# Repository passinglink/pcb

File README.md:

### Passing Link PCB designs
This is a dumping ground for PCB designs for [Passing Link](https://github.com/passinglink/passinglink).

Designs are implemented in [Horizon EDA](https://horizon-eda.org/). To load them, add `./pool` to
your pools in Horizon's settings.

Current designs:
- [microdash](microdash/) - a minimal hitbox
- [module](module/) - passinglink on an M.2 module, that can be assembled directly by JLCPCB
  - [panthera](panthera/) - an adapter board for `module`

Legacy KiCAD designs:
  - Razer Panthera
    - [STM32](panthera_stm32/)
    - [NRF52840](panthera_e73/)

### Copying
Unless otherwise specified, everything in this repository is licensed under the MIT license.

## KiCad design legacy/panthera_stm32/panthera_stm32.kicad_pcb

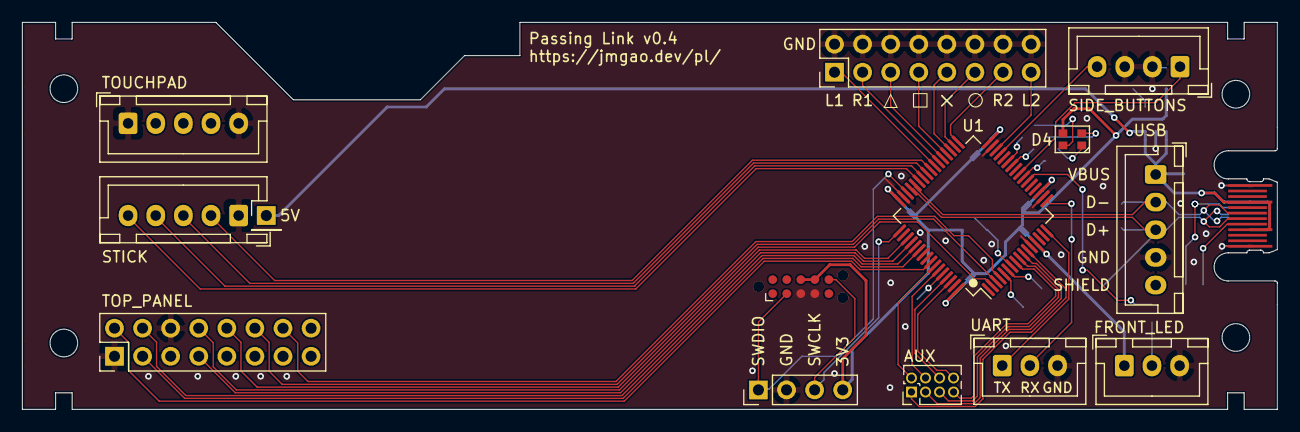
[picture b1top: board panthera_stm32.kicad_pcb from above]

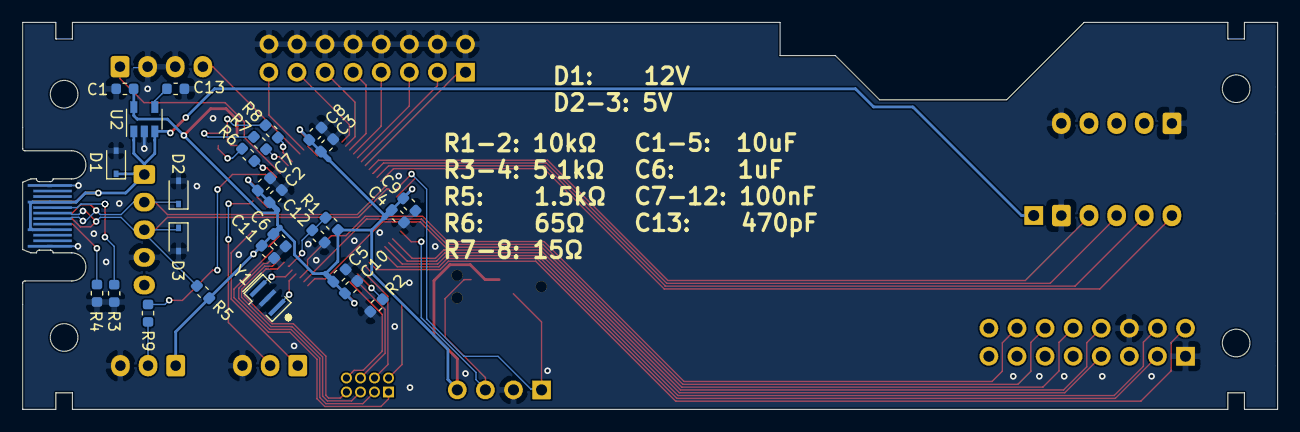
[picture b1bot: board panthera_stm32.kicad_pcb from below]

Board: 2 copper layers, 113.5 x 35.0 mm, 47 parts (32 on the bottom side), 59 nets.

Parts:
C1, C2, C3, C4, C5: 10uF; C_0603_1608Metric
C6: 1uF; C_0603_1608Metric
C7, C8, C9, C10, C11, C12: 100nF; C_0603_1608Metric
C13: 470pF; C_0603_1608Metric
D1: PESD12VL1BA,115; D_SOD-323
D2, D3: PESD5V0L1BA,115; D_SOD-323
D4: FM-B2020RGBA-HG
J1: Conn_01x05_Female; JST_XH_B5B-XH-A_1x05_P2.50mm_Vertical
J2: Conn_01x04; PinHeader_1x04_P2.54mm_Vertical
J3: Conn_02x05_Odd_Even; Tag-Connect_TC2050-IDC-NL_2x05_P1.27mm_Vertical
J4, J5: Conn_01x05; JST_XH_B5B-XH-A_1x05_P2.50mm_Vertical
J6, J7: Conn_02x08_Odd_Even; PinHeader_2x08_P2.54mm_Vertical
J8, J9: Conn_01x03; JST_XH_B3B-XH-A_1x03_P2.50mm_Vertical
J10: Conn_02x04_Odd_Even; PinHeader_2x04_P1.27mm_Vertical
J11: Conn_01x01; PinHeader_1x01_P2.54mm_Vertical
J12: Conn_01x04; JST_XH_B4B-XH-A_1x04_P2.50mm_Vertical
NT1, NT2, NT3, NT4, NT5: Net-Tie_2; NetTie-2_SMD_Pad0.5mm
R1, R2: 10K; R_0603_1608Metric
R3, R4: 5.1K; R_0603_1608Metric
R5: 1.5K; R_0603_1608Metric
R6: 65; R_0603_1608Metric
R7, R8: 15; R_0603_1608Metric
R9: 100; R_0603_1608Metric
U1: STM32F103RETx; LQFP-64_10x10mm_P0.5mm
U2: MIC5219-3.3YM5; SOT-23-5
X1: PCB-USB-C
Y1: Crystal_GND2_Small; Resonator_SMD_muRata_CSTxExxV-3Pin_3.0x1.1mm

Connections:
+3V3: C1.1, D4.3, J2.4, J3.7, J3.8, NT1.1, NT2.1, NT3.1, NT4.1, NT5.1, R1.2, U2.5
/BOOT0: R2.1, U1.60
/NRST: C12.1, R1.1, U1.7
/OSC_IN: U1.5, Y1.3
/OSC_OUT: U1.6, Y1.1
/PA2_UART_TX: J9.1, U1.16
/PA3_UART_RX: J9.2, U1.17
/PA6_FRONT_LED_K: R9.2, U1.22
/PA7_LED_R_K: R6.1, U1.23
/PA8_STICK_LEFT: J5.3, U1.41
/PA9_STICK_UP: J5.4, U1.42
/PA10_STICK_DOWN: J5.5, U1.43
/PB0_LED_G_K: R7.1, U1.26
/PB1_LED_B_K: R8.1, U1.27
/PB5_BUTTON_TOUCHPAD: J7.2, U1.57
/PB6: J10.2, U1.58
/PB7: J10.4, U1.59
/PB8: J10.6, U1.61
/PB9: J10.8, U1.62
/PB10_SELECT: J12.4, U1.29
/PB11_BUTTON_L2: J6.15, U1.30
/PB12_BUTTON_R2: J6.13, U1.33
/PB13_BUTTON_CIRCLE: J6.11, U1.34
/PB14_BUTTON_CROSS: J6.9, U1.35
/PB15_BUTTON_SQUARE: J6.7, U1.36
/PC0: J10.7, U1.8
/PC1: J10.5, U1.9
/PC2: J10.3, U1.10
/PC3: J10.1, U1.11
/PC4_START: J12.1, U1.24
/PC6_BUTTON_TRIANGLE: J6.5, U1.37
/PC7_BUTTON_R1: J6.3, U1.38
/PC8_BUTTON_L1: J6.1, U1.39
/PC9_STICK_RIGHT: J5.2, U1.40
/PC10_MODE_RS: J7.8, U1.51
/PC11_MODE_PS3: J7.7, U1.52
/PC12_BUTTON_L3: J7.4, U1.53
/PC13_MODE_LS: J7.10, U1.2
/PC14_MODE_LOCK: J7.12, U1.3
/PC15_BUTTON_PS4: J7.14, U1.4
/PD2_BUTTON_R3: J7.3, U1.54
GND: C1.2, C2.2, C3.2, C4.2, C5.2, C6.2, C7.2, C8.2, C9.2, C10.2, C11.2, C12.2, C13.2, D1.2, D2.2, D3.2, J1.4, J2.2, J3.3, J3.4, J4.1, J4.5, J5.1, J6.2, J6.4, J6.6, J6.8, J6.10, J6.12, J6.14, J6.16, J7.1, J7.6, J8.3, J9.3, J12.2, J12.3, R2.2, R3.2, R4.2, U1.12, U1.18, U1.31, U1.47, U1.63, U2.2, X1.A1, X1.A12, X1.B1, X1.B12, Y1.2
unnamed: C13.1, U2.4
unnamed: D4.1, R6.2
unnamed: D4.2, R8.2
unnamed: D4.4, R7.2
unnamed: J8.2, R9.1
unnamed: R3.1, X1.B5
unnamed: R4.1, X1.A5
SWCLK: J2.3, J3.6, U1.49
SWDIO: J2.1, J3.2, U1.46
USB_D+: D3.1, J1.3, R5.1, U1.45, X1.A6, X1.B6
USB_D-: D2.1, J1.2, U1.44, X1.A7, X1.B7
USB_VBUS: D1.1, J1.1, J11.1, U2.1, U2.3, X1.A4, X1.A9, X1.B4, X1.B9
VCC1: C2.1, C7.1, NT1.2, U1.19
VCC2: C3.1, C8.1, NT2.2, U1.32
VCC3: C4.1, C9.1, NT3.2, U1.48
VCC4: C5.1, C10.1, NT4.2, U1.64
VDDA: C6.1, C11.1, J8.1, NT5.2, R5.2, U1.13

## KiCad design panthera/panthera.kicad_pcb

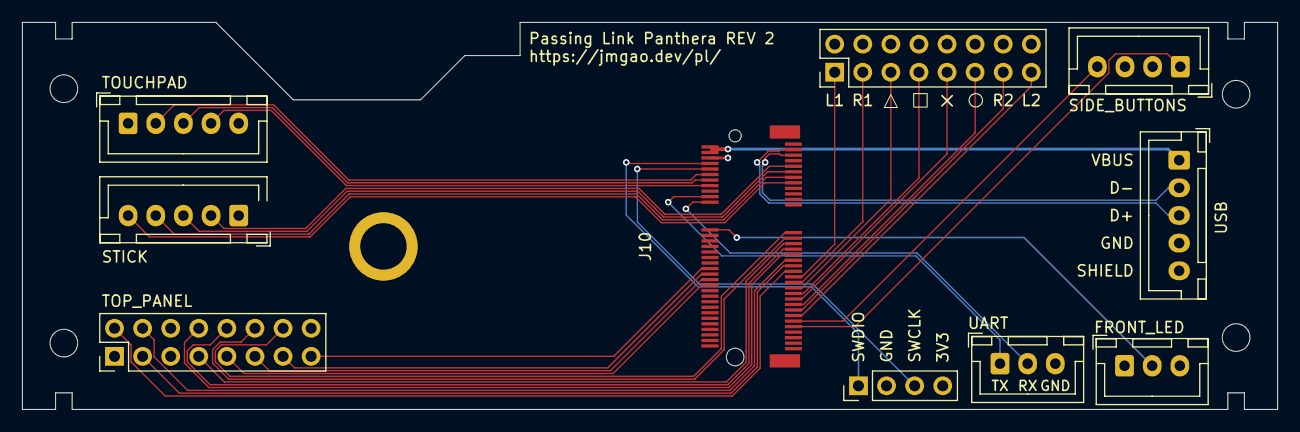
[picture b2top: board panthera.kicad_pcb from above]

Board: 2 copper layers, 113.5 x 35.0 mm, 10 parts (0 on the bottom side), 39 nets.

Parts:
J1: Conn_01x05_Female; JST_XH_B5B-XH-A_1x05_P2.50mm_Vertical
J2: Conn_01x04; PinHeader_1x04_P2.54mm_Vertical
J4, J5: Conn_01x05; JST_XH_B5B-XH-A_1x05_P2.50mm_Vertical
J6, J7: Conn_02x08_Odd_Even; PinHeader_2x08_P2.54mm_Vertical
J8, J9: Conn_01x03; JST_XH_B3B-XH-A_1x03_P2.50mm_Vertical
J10: PassingLink_NGFF-E; PassingLink_Module
J12: Conn_01x04; JST_XH_B4B-XH-A_1x04_P2.50mm_Vertical

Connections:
+3V3: J2.4, J7.16, J8.1, J10.6
/BUTTON_CIRCLE: J6.11, J10.59
/BUTTON_CROSS: J6.9, J10.57
/BUTTON_L1: J6.1, J10.49
/BUTTON_L2: J6.15, J10.63
/BUTTON_L3: J7.4, J10.43
/BUTTON_PS4: J7.14, J10.33
/BUTTON_R1: J6.3, J10.51
/BUTTON_R2: J6.13, J10.61
/BUTTON_R3: J7.3, J10.45
/BUTTON_SELECT: J10.65, J12.4
/BUTTON_SQUARE: J6.7, J10.55
/BUTTON_START: J10.67, J12.1
/BUTTON_TOUCHPAD: J7.2, J10.47
/BUTTON_TRIANGLE: J6.5, J10.53
/LED_FRONT_K: J8.2, J10.32
/LED_P1_K: J7.15, J10.46
/LED_P2_K: J7.13, J10.48
/LED_P3_K: J7.11, J10.50
/LED_P4_K: J7.9, J10.52
/MODE_LOCK: J7.12, J10.35
/MODE_LS: J7.10, J10.39
/MODE_PS3: J7.7, J10.37
/MODE_RS: J7.8, J10.41
/STICK_DOWN: J5.5, J10.15
/STICK_LEFT: J5.3, J10.11
/STICK_RIGHT: J5.2, J10.9
/STICK_UP: J5.4, J10.13
/SWCLK: J2.3, J10.10
/SWDIO: J2.1, J10.8
/TP_RST: J4.4, J10.16
/TP_SCL: J4.2, J10.12
/TP_SDA: J4.3, J10.14
/UART_RX: J9.2, J10.22
/UART_TX: J9.1, J10.20
GND: J1.4, J2.2, J4.1, J4.5, J5.1, J6.2, J6.4, J6.6, J6.8, J6.10, J6.12, J6.14, J6.16, J7.1, J7.6, J8.3, J9.3, J10.1, J10.7, J12.2, J12.3
USB_D+: J1.3, J10.3
USB_D-: J1.2, J10.5
USB_VBUS: J1.1, J10.2, J10.4

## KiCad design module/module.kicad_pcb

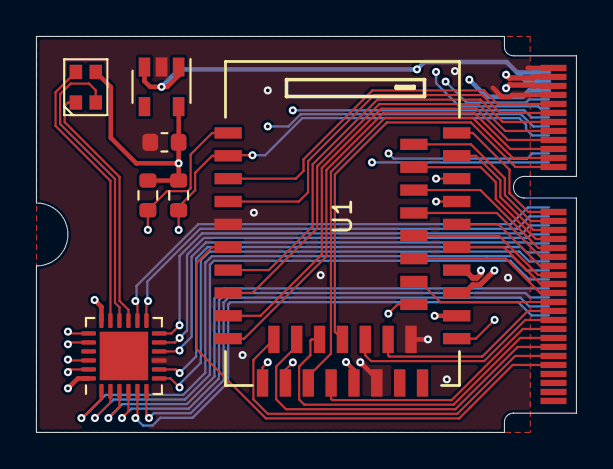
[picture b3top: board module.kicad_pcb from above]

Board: 4 copper layers, 30.0 x 22.0 mm, 8 parts (0 on the bottom side), 55 nets.

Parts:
C1: 1uF; C_0603_1608Metric
D1: FM-B2020RGBA-HG
J1: PassingLink_NGFF-E; NGFF_E
R1, R2: 10K; R_0603_1608Metric
U1: E73-2G4M08S1C
U2: MIC5219-3.3YM5; SOT-23-5
U3: AW9523BTQR; QFN-24-1EP_4x4mm_P0.5mm_EP2.7x2.7mm

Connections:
+3V3: C1.1, D1.3, J1.6, R1.1, R2.1, U1.19, U2.5, U3.18, U3.24
/A0: J1.9, U1.3
/A1: J1.11, U1.4
/A2: J1.13, U1.7
/A3: J1.15, U1.8
/A4: J1.17, U1.9
/A5: J1.19, U1.10
/A6: J1.21, U1.15
/A7: J1.23, U1.18
/AUX0: J1.56, U3.5
/AUX1: J1.54, U3.6
/AUX2: J1.44, U3.7
/AUX3: J1.42, U3.8
/AUX4: J1.40, U3.10
/AUX5: J1.38, U3.11
/AUX6: J1.36, U3.12
/AUX7: J1.34, U3.13
/AUX8: J1.46, U3.1
/AUX9: J1.48, U3.2
/AUX10: J1.50, U3.3
/AUX11: J1.52, U3.4
/AUX12: J1.32, U3.14
/D0: J1.33, U1.43
/D1: J1.35, U1.42
/D2: J1.37, U1.41
/D3: J1.39, U1.40
/D4: J1.41, U1.38
/D5: J1.43, U1.36
/D6: J1.45, U1.35
/D7: J1.47, U1.34
/D8: J1.49, U1.33
/D9: J1.51, U1.32
/D10: J1.53, U1.30
/D11: J1.55, U1.22
/D12: J1.57, U1.20
/D13: J1.59, U1.17
/D14: J1.61, U1.16
/D15: J1.63, U1.14
/D16: J1.65, U1.12
/D17: J1.67, U1.6
/I2C0_SCL: J1.12, U1.13, U3.19
/I2C0_SDA: J1.14, U1.11, U3.20
/LED_B_K: D1.2, U3.17
/LED_G_K: D1.4, U3.16
/LED_R_K: D1.1, U3.15
/SWDCLK: J1.10, U1.39
/SWDIO: J1.8, U1.37
/UART_RX: J1.22, U1.28
/UART_TX: J1.20, U1.26
/USB_D+: J1.3, U1.31
/USB_D-: J1.5, U1.29
/~GPIO_INT: R1.2, U1.1, U3.22
/~I2C0_RST: J1.16, R2.2, U1.2, U3.23
GND: C1.2, J1.1, J1.7, U1.5, U1.21, U1.24, U2.2, U3.9
USB_VBUS: J1.2, J1.4, U1.27, U2.1, U2.3

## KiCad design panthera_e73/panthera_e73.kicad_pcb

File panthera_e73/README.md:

## Razer Panthera PCB (E73-2G4M08S1C)

Drop in replacement for the Razer Panthera's PCB, with on-board [Tag-Connect](https://www.tag-connect.com/) connector, and USB-C connector (use 0.8mm thickness if you want to use this).

### TODO in next revision
- [ ] Sound output IC?
- [ ] Define a protocol to identify specific boards for GPIO mapping

### BOM

| Part type  | Part number            | Quantity | Cost per individual item                                     |
|------------|------------------------|----------|--------------------------------------------------------------|
| MCU Module | E73-2G4M08S1C          | 1        | [$4.39](https://www.aliexpress.com/item/32906661666.html)    |
| LDO        | MIC5219-3.3YM5         | 1        | [$0.10](https://www.ebay.com/sch/i.html?_nkw=MIC5219-3.3YM5) |
| Diode      | PESD12VL1BA,115        | 1        | [$0.05](https://lcsc.com/search?q=C38558)                    |
| Diode      | PESD5V0L1BA,115        | 2        | [$0.04](https://lcsc.com/search?q=C85380)                    |
| Pin header | Generic 0.1" 2x10 male | 2        | [$0.05](https://lcsc.com/search?q=C68234)                    |
| Pin header | Generic 0.1" 1x4 male  | 1        | [$0.02](https://lcsc.com/search?q=C358686)                   |
| Connector  | JST B5B-XH-AM          | 3        | [$0.10](https://lcsc.com/search?q=C161872)                   |
| Connector  | JST B4B-XH-AM          | 1        | [$0.08](https://lcsc.com/search?q=C161871)                   |
| Connector  | JST B3B-XH-AM          | 2        | [$0.07](https://lcsc.com/search?q=C161870)                   |
| Resistor   | 0603 10kΩ              | 1        | ~$0                                                          |
| Resistor   | 0603 5.1kΩ             | 2        | ~$0                                                          |
| Resistor   | 0603 100kΩ             | 1        | ~$0                                                          |

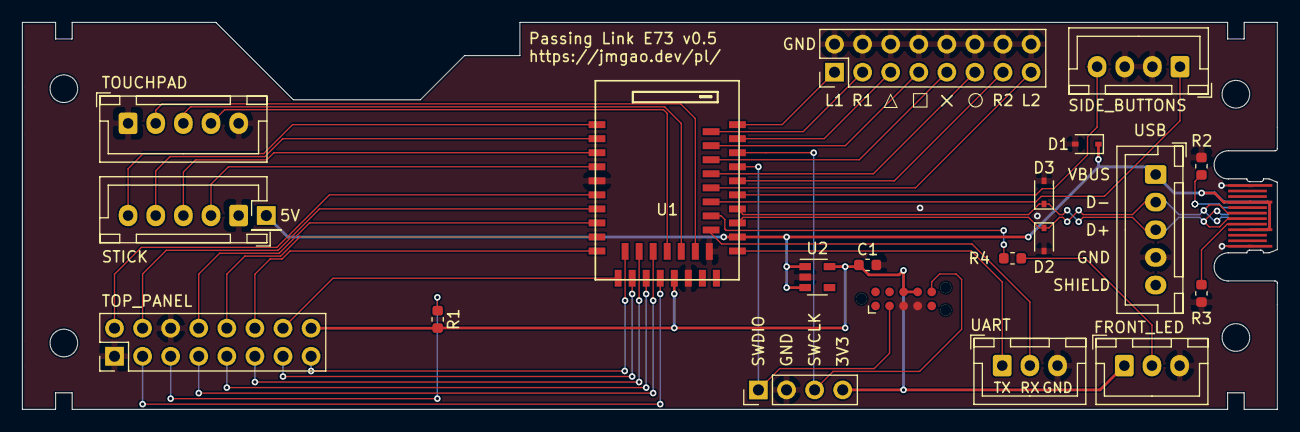
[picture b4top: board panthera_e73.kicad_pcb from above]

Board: 2 copper layers, 113.5 x 35.0 mm, 22 parts (0 on the bottom side), 42 nets.

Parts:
C1: 1uF; C_0603_1608Metric
D1: PESD12VL1BA,115; D_SOD-323
D2, D3: PESD5V0L1BA,115; D_SOD-323
J1: Conn_01x05_Female; JST_XH_B5B-XH-A_1x05_P2.50mm_Vertical
J2: Conn_01x04; PinHeader_1x04_P2.54mm_Vertical
J3: Conn_02x05_Odd_Even; Tag-Connect_TC2050-IDC-NL_2x05_P1.27mm_Vertical
J4, J5: Conn_01x05; JST_XH_B5B-XH-A_1x05_P2.50mm_Vertical
J6, J7: Conn_02x08_Odd_Even; PinHeader_2x08_P2.54mm_Vertical
J8, J9: Conn_01x03; JST_XH_B3B-XH-A_1x03_P2.50mm_Vertical
J11: Conn_01x01; PinHeader_1x01_P2.54mm_Vertical
J12: Conn_01x04; JST_XH_B4B-XH-A_1x04_P2.50mm_Vertical
R1: 10K; R_0603_1608Metric
R2, R3: 5.1K; R_0603_1608Metric
R4: 100; R_0603_1608Metric
U1: E73-2G4M08S1C
U2: MIC5219-3.3YM5; SOT-23-5
X1: PCB-USB-C

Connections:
+3V3: C1.1, J2.4, J3.7, J3.8, J7.16, J8.1, R1.2, U1.19, U2.5
/BUTTON_CIRCLE: J6.11, U1.36
/BUTTON_CROSS: J6.9, U1.38
/BUTTON_L1: J6.1, U1.43
/BUTTON_L2: J6.15, U1.34
/BUTTON_L3: J7.4, U1.7
/BUTTON_PS4: J7.14, U1.11
/BUTTON_R1: J6.3, U1.42
/BUTTON_R2: J6.13, U1.35
/BUTTON_R3: J7.3, U1.17
/BUTTON_SELECT: J12.4, U1.33
/BUTTON_SQUARE: J6.7, U1.40
/BUTTON_START: J12.1, U1.32
/BUTTON_TOUCHPAD: J7.2, U1.6
/BUTTON_TRIANGLE: J6.5, U1.41
/LED_FRONT_K: R4.2, U1.30
/LED_P1_K: J7.15, U1.12
/LED_P2_K: J7.13, U1.13
/LED_P3_K: J7.11, U1.14
/LED_P4_K: J7.9, U1.15
/MODE_LOCK: J7.12, U1.10
/MODE_LS: J7.10, U1.9
/MODE_PS3: J7.7, U1.16
/MODE_RS: J7.8, U1.8
/STICK_DOWN: J5.5, U1.1
/STICK_LEFT: J5.3, U1.3
/STICK_RIGHT: J5.2, U1.4
/STICK_UP: J5.4, U1.2
/TP_INT: J7.5, R1.1
/TP_SCL: J4.2, U1.20
/TP_SDA: J4.3, U1.18
/UART_RX: J9.2, U1.28
/UART_TX: J9.1, U1.26
GND: C1.2, D1.2, D2.2, D3.2, J1.4, J2.2, J3.3, J3.4, J4.1, J4.5, J5.1, J6.2, J6.4, J6.6, J6.8, J6.10, J6.12, J6.14, J6.16, J7.1, J7.6, J8.3, J9.3, J12.2, J12.3, R2.2, R3.2, U1.5, U1.21, U1.24, U2.2, X1.A1, X1.A12, X1.B1, X1.B12
unnamed: J8.2, R4.1
unnamed: R2.1, X1.B5
unnamed: R3.1, X1.A5
SWCLK: J2.3, J3.6, U1.39
SWDIO: J2.1, J3.2, U1.37
USB_D+: D3.1, J1.3, U1.31, X1.A6, X1.B6
USB_D-: D2.1, J1.2, U1.29, X1.A7, X1.B7
USB_VBUS: D1.1, J1.1, J11.1, U1.27, U2.1, U2.3, X1.A4, X1.A9, X1.B4, X1.B9

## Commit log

2020-02-27 Import Panthera PCB from jmgao/passinglink.
2020-02-27 Rename panthera to panthera_stm32.
2020-03-01 Add CDEbyte E73 variant of Panthera board.
2020-03-13 e73: fix mislabeled touchpad pins.
    Thankfully, the NRF52 can remap its pins arbitrarily, and the interrupt
    pin is non-crucial, so no actual change is necessary.
2020-03-14 e73: fix mislabeled controller number LED pins.
2020-03-14 e73: add some notes about optional parts.
2021-01-17 Center the E73 symbol.
2021-01-21 Add NGFF module design.
2021-02-01 Initial commit of empty pool.
2021-02-05 pool: add E73-2G4M08S1C.
2021-02-05 pool: add RT9078-33GQZ.
2021-02-05 pool: add TLV320DAC3203IRGET.
2021-02-05 pool: add SN74LVC1GX04DRLR.
2021-02-05 pool: add AW9523BTQ.
2021-02-05 pool: add on-board NGFF connector.
2021-02-05 pool: add FM-B2020RGBA-HG.
2021-02-05 pool: add CSTNE12M2G55A000R0.
2021-02-05 pool: add NASE0-S6701-TSH4.
2021-02-05 pool: add generic through-hole capacitor.
2021-02-05 pool: add JST-XH connectors.
2021-02-05 Add panthera adapter board.
2021-02-05 Implement PassingLink NGFF module.
2021-02-17 pool: add DX07S016JA1.
2021-02-18 pool: add Kailh Choc socket.
2021-02-18 pool: add PRTR5V0U2F.
2021-02-18 pool: add MIC5219-3.3BMM.
2021-02-18 pool: add XC8102.
2021-02-18 pool: add Keystone 4882.
2021-02-25 microdash: shrink keyswitch top cutout.
2021-02-25 microdash: add paste to through-holes.
2021-02-25 microdash: add.
2021-02-25 microdash: shrink keyswitch alignment holes.
2021-03-13 microdash: revision 2.
    - Switch from the diode array to discrete TVS diodes for ease of
    assembly.
    - Drop the current sense resistors.
    - Abandon the idea of using paste to solder the keyswitch sockets.
    - Move the LED controllers and OLED to separate I2C buses.
    - Switch to a regulator that's stable with ceramic caps to drop a resistor.
2021-03-15 microdash: move exported files to their own directory.
2021-03-15 Move KiCAD designs to their own folder.
2021-03-15 Add README for horizon designs.
2021-03-15 Remove reference to proprietary JAE 3d model.
2021-03-15 Migrate module/panthera to latest Horizon version.
